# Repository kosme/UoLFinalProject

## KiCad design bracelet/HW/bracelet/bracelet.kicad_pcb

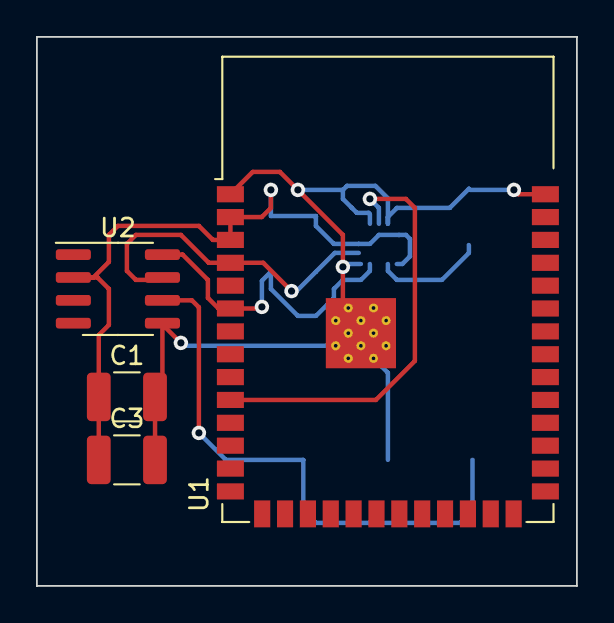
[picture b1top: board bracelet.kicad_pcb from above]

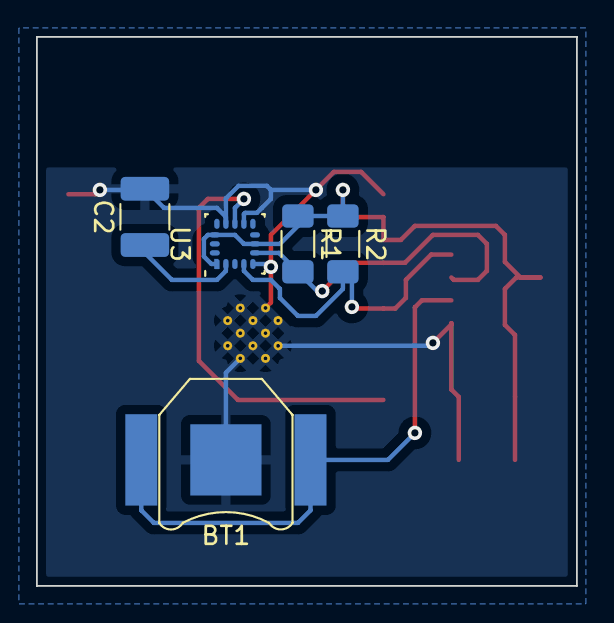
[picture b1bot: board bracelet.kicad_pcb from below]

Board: 2 copper layers, 30.0 x 30.5 mm, 9 parts (5 on the bottom side), 7 nets.

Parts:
BT1: Battery_Cell; BatteryHolder_Keystone_2998_1x6.8mm
C1, C2: 0.1uF; C_1210_3225Metric_Pad1.33x2.70mm_HandSolder
C3: 4.7uF; C_1210_3225Metric_Pad1.33x2.70mm_HandSolder
R1, R2: 4K7; R_1206_3216Metric_Pad1.30x1.75mm_HandSolder
U1: ESP32-S3-WROOM-1
U2: DS3231MZ; SOIC-8_3.9x4.9mm_P1.27mm
U3: MMA8542Q; Freescale-QFN-16_3x3_Pitch0.5mm

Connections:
+3V3: C1.1, C3.1, R1.1, R2.1, U1.2 (VDD), U1.3 (EN), U2.2 (VCC), U3.1 (VDDIO), U3.7 (SA0), U3.14 (Vdd)
GND: BT1.2 (-), C1.2, C2.2, C3.2, U1.1 (GND), U1.40 (GND), U1.41 (GND), U2.5 (GND), U3.5 (Gnd), U3.10 (Gnd), U3.12 (Gnd)
unnamed: BT1.1 (+), U2.6 (VBAT)
unnamed: C2.1, U3.2 (BYP)
unnamed: R1.2, U1.4 (IO4), U2.7 (SDA), U3.6 (SDA)
unnamed: R2.2, U1.6 (IO6), U2.8 (SCL), U3.4 (SCL)
unnamed: U1.10 (IO17), U3.11 (INT1)

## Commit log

2023-03-27 final project delivery
2023-12-14 Correct server code
2023-12-14 Add missing django files
